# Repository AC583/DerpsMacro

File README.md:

BOM:

- 8x Cherry MX Switches
- 2x SK6812 MINI Leds
- 1x XIAO RP2040
- 8x Blank DSA Keycaps
- 9x M3x16 Bolt
- 9x M3 Heatset
- 1x EC11 Rotary encoders with push-button switch

PCB:

Schematic

Top Case

Bottom Case

Full Case

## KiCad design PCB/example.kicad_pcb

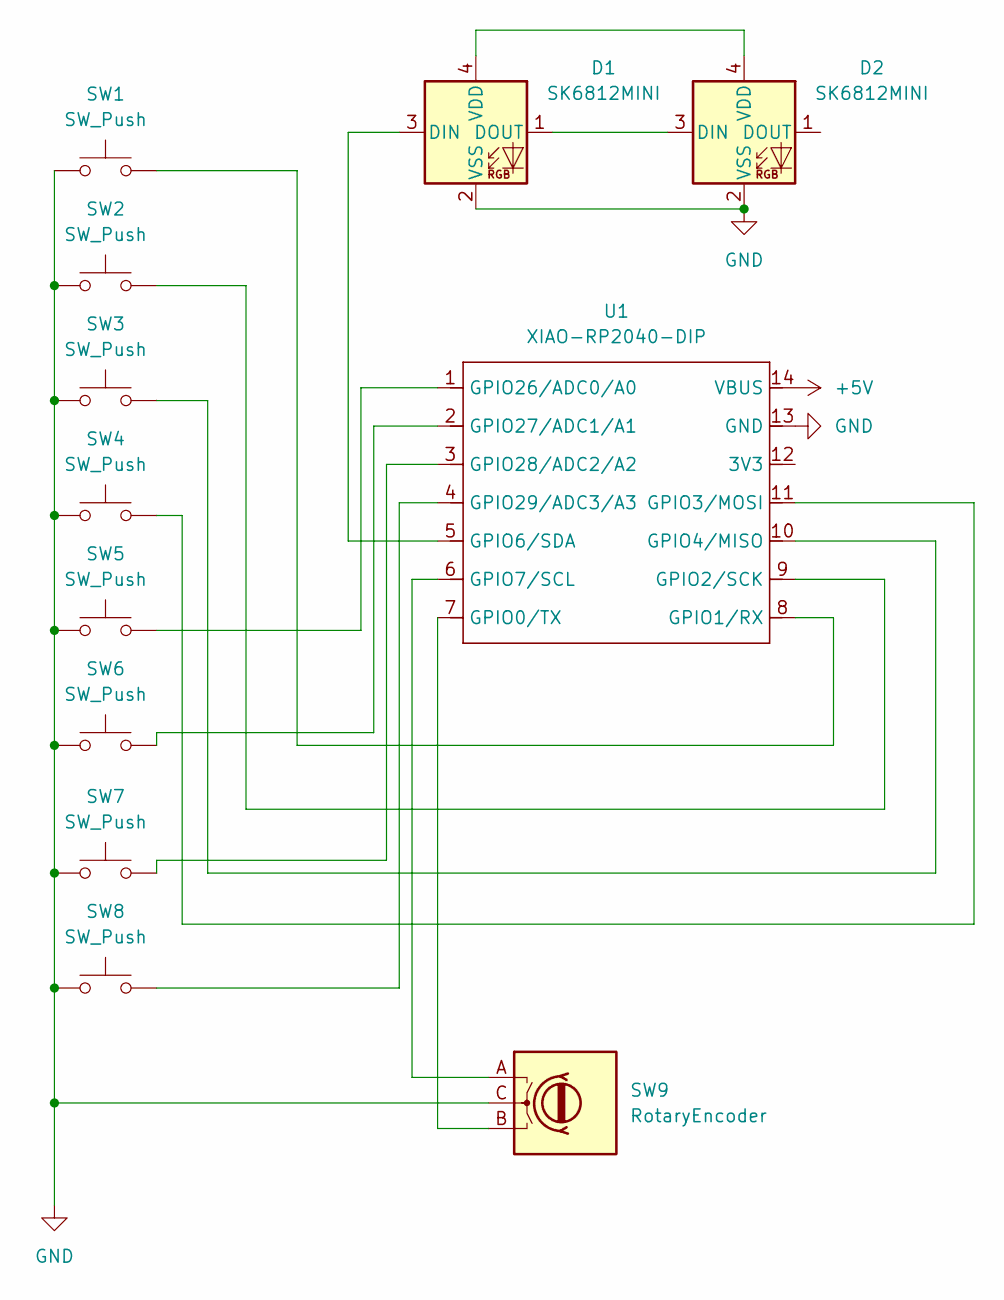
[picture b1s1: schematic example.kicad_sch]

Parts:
D1, D2: SK6812MINI; LED_SK6812MINI_PLCC4_3.5x3.5mm_P1.75mm
SW1, SW2, SW3, SW4, SW5, SW6, SW7, SW8: SW_Push; SW_Cherry_MX_1.00u_PCB
SW9: RotaryEncoder; RotaryEncoder_Alps_EC11E-Switch_Vertical_H20mm_CircularMoun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
U1: XIAO-RP2040-DIP

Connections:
+5V: U1.14 (VBUS)
GND: D1.2 (VSS), D2.2 (VSS), SW1.1, SW2.1, SW3.1, SW4.1, SW5.1, SW6.1, SW7.1, SW8.1, SW9.C, U1.13 (GND)
unnamed: D1.3 (DIN), U1.5 (GPIO6/SDA)
unnamed: D1.1 (DOUT), D2.3 (DIN)
unnamed: D1.4 (VDD), D2.4 (VDD)
unnamed: SW9.B, U1.7 (GPIO0/TX)
unnamed: SW1.2, U1.8 (GPIO1/RX)
unnamed: SW2.2, U1.9 (GPIO2/SCK)
unnamed: SW4.2, U1.11 (GPIO3/MOSI)
unnamed: SW3.2, U1.10 (GPIO4/MISO)
unnamed: SW9.A, U1.6 (GPIO7/SCL)
unnamed: SW5.2, U1.1 (GPIO26/ADC0/A0)
unnamed: SW6.2, U1.2 (GPIO27/ADC1/A1)
unnamed: SW7.2, U1.3 (GPIO28/ADC2/A2)
unnamed: SW8.2, U1.4 (GPIO29/ADC3/A3)

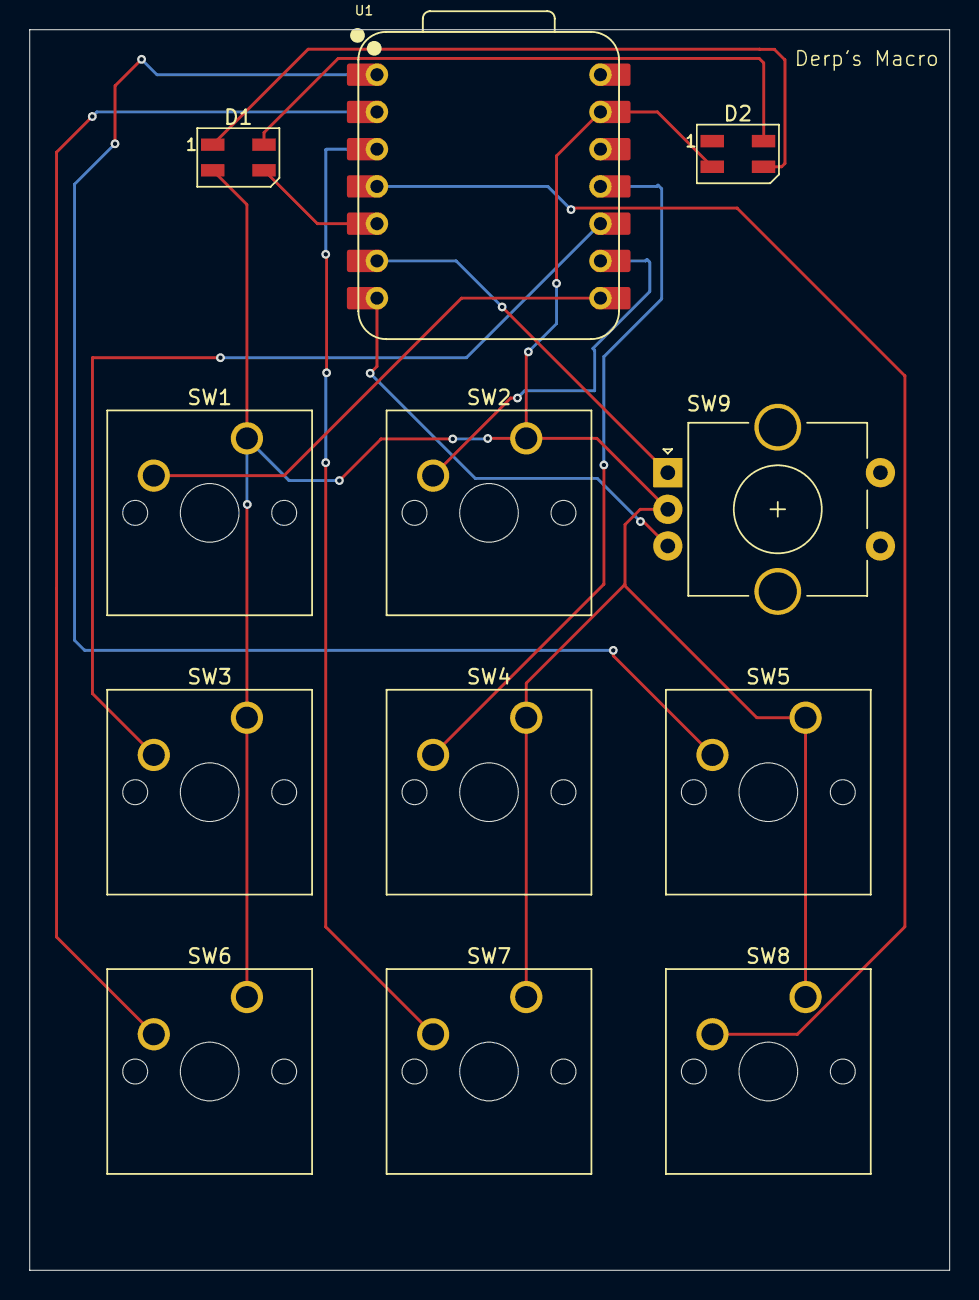
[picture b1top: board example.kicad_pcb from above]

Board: 2 copper layers, 62.7 x 84.6 mm, 12 parts (0 on the bottom side), 14 nets.

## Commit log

2025-12-10 Second commit
2025-12-10 Third commit
2025-12-10 Fourth commit
2025-12-10 FIfrth commit
2025-12-19 laptop
2025-12-23 Sixth commit
2025-12-23 Seventh commit
2025-12-23 Eight commit
